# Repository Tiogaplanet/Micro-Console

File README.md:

# Micro-Console
 An Arduboy clone.  I can't think of a witty name.

# Background
This started as a simple project to throw together a PCB with some buttons and an OLED display on which my kids could learn programming and be entertained.  While googling my way to get started I discovered, of course, something like this has already been done and it's called the Arduboy.  It comes with a huge library of games, several community-driven spin-offs, and ports to different MCUs.  There's also the Gamebuino and a bunch of one-off creations enthusiasts have developed but we're going to stick with the Arduboy design here.  Why give up such a huge library of existing software and the community support?

# Design
This project, like the Arduboy, is based on the ATmega32u4.  I'd prefer to use my beloved Wemos D1 mini but I'd rather not use or maintain a ported library, nor do I care to work around the limited IO of the D1 mini.  When the time comes to add Internet access to this device, I will add some form of the ESP8266 with its own library that can co-exist with the Arduboy's library.  This project includes the Winbond W25Q128 SPI flash memory device used in the Arduboy FX.

# Credit
Naturally, credit is owed to Kevin Bates for instigating the whole Arduboy endeavor.

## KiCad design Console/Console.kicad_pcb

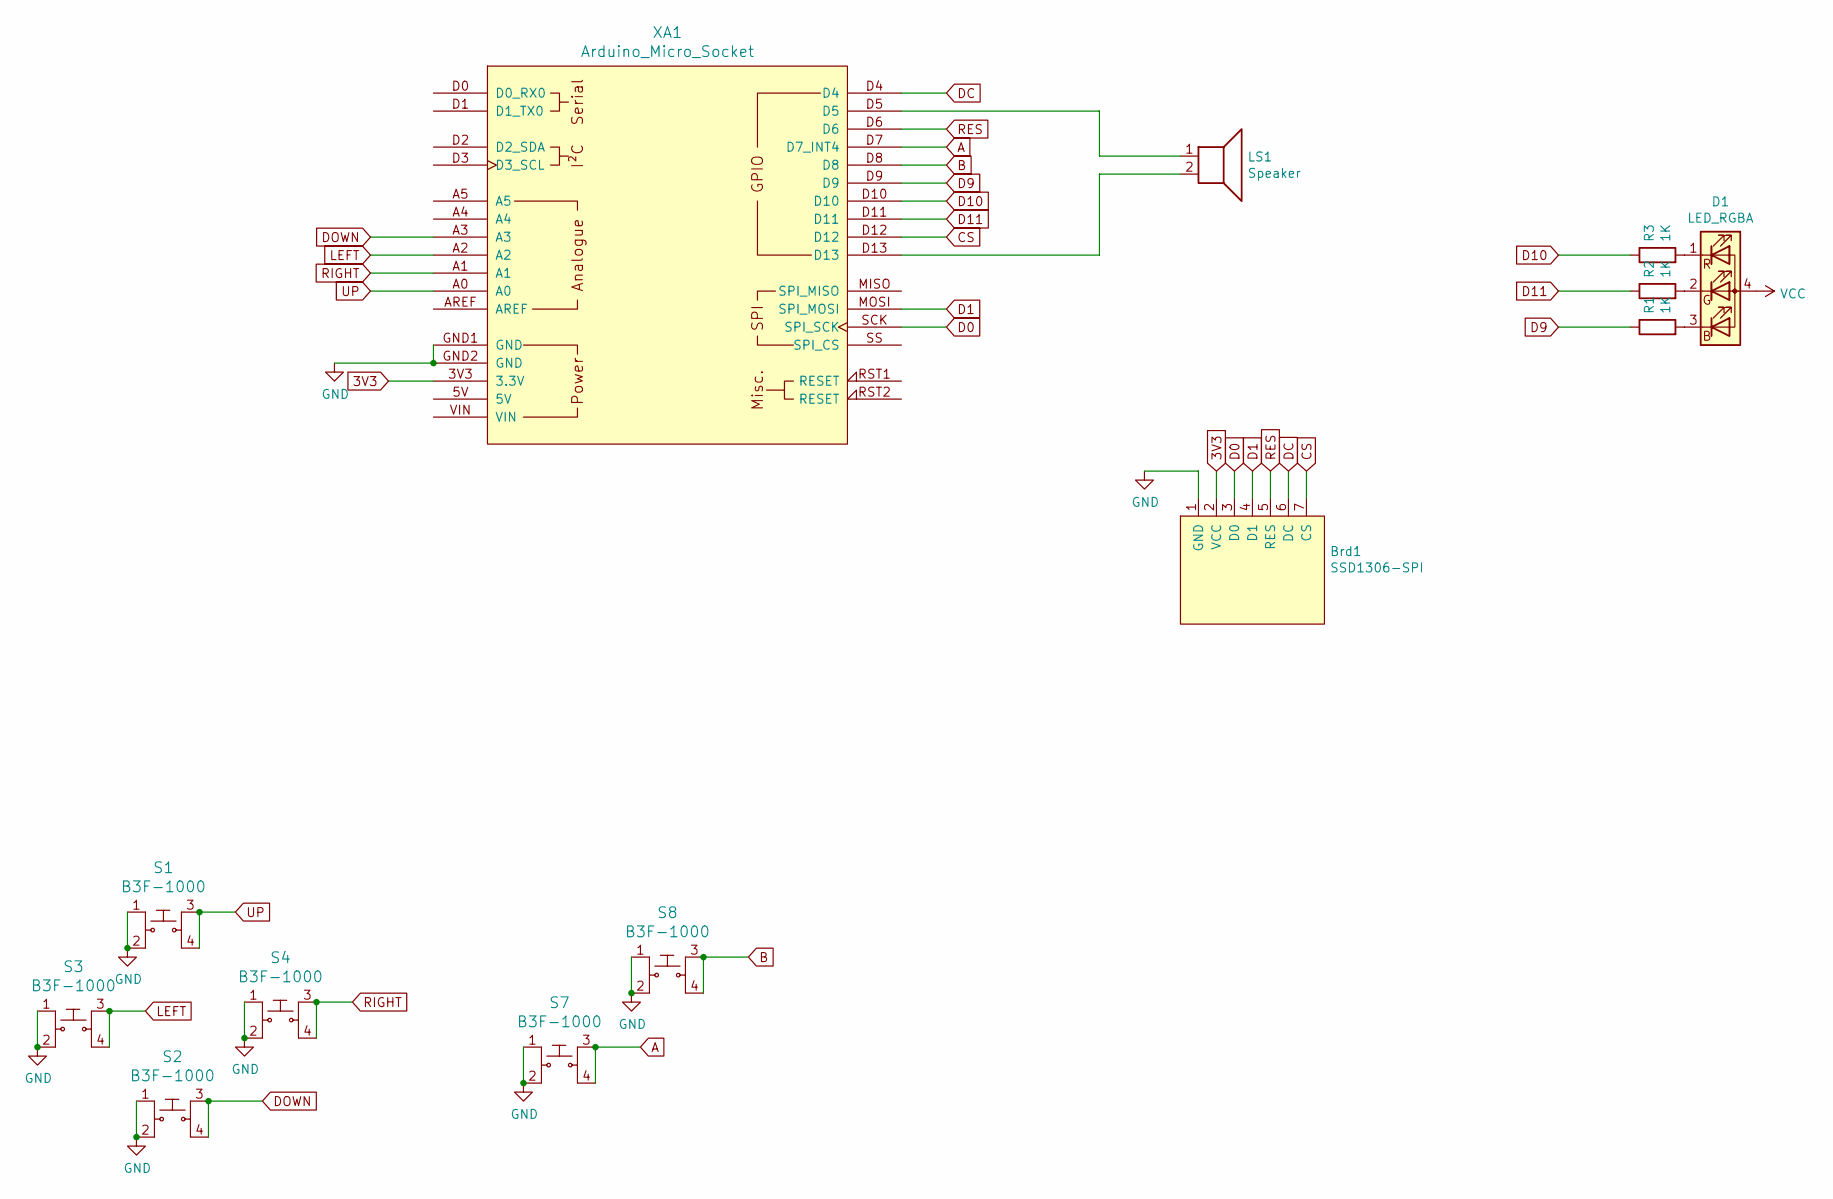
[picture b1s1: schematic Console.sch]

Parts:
Brd1: SSD1306-SPI; 128x64-OLED-SPI
D1: LED_RGBA; LED_BL-FL7680RGB
LS1: Speaker; Buzzer_D14mm_H7mm_P10mm
R1, R2, R3: 1K; R_Axial_DIN0207_L6.3mm_D2.5mm_P7.62mm_Horizontal
S1, S2, S3, S4, S7, S8: B3F-1000; Switch_Tactile_THT_B3F-1xxx; MPN B3F-1000; Digi-Key_PN SW400-ND
XA1: Arduino_Micro_Socket

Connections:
3V3: Brd1.2 (VCC), XA1.3V3 (3.3V)
A: S7.3, S7.4, XA1.D7 (D7_INT4)
B: S8.3, S8.4, XA1.D8
CS: Brd1.7 (CS), XA1.D12
D0: Brd1.3 (D0), XA1.SCK (SPI_SCK)
D1: Brd1.4 (D1), XA1.MOSI (SPI_MOSI)
D9: R1.1, XA1.D9
D10: R3.1, XA1.D10
D11: R2.1, XA1.D11
DC: Brd1.6 (DC), XA1.D4
DOWN: S2.3, S2.4, XA1.A3
GND: Brd1.1 (GND), S1.1, S1.2, S2.1, S2.2, S3.1, S3.2, S4.1, S4.2, S7.1, S7.2, S8.1, S8.2, XA1.GND1 (GND), XA1.GND2 (GND)
LEFT: S3.3, S3.4, XA1.A2
unnamed: D1.1 (RK), R3.2
unnamed: D1.2 (GK), R2.2
unnamed: D1.3 (BK), R1.2
unnamed: LS1.1, XA1.D5
unnamed: LS1.2, XA1.D13
RES: Brd1.5 (RES), XA1.D6
RIGHT: S4.3, S4.4, XA1.A1
UP: S1.3, S1.4, XA1.A0

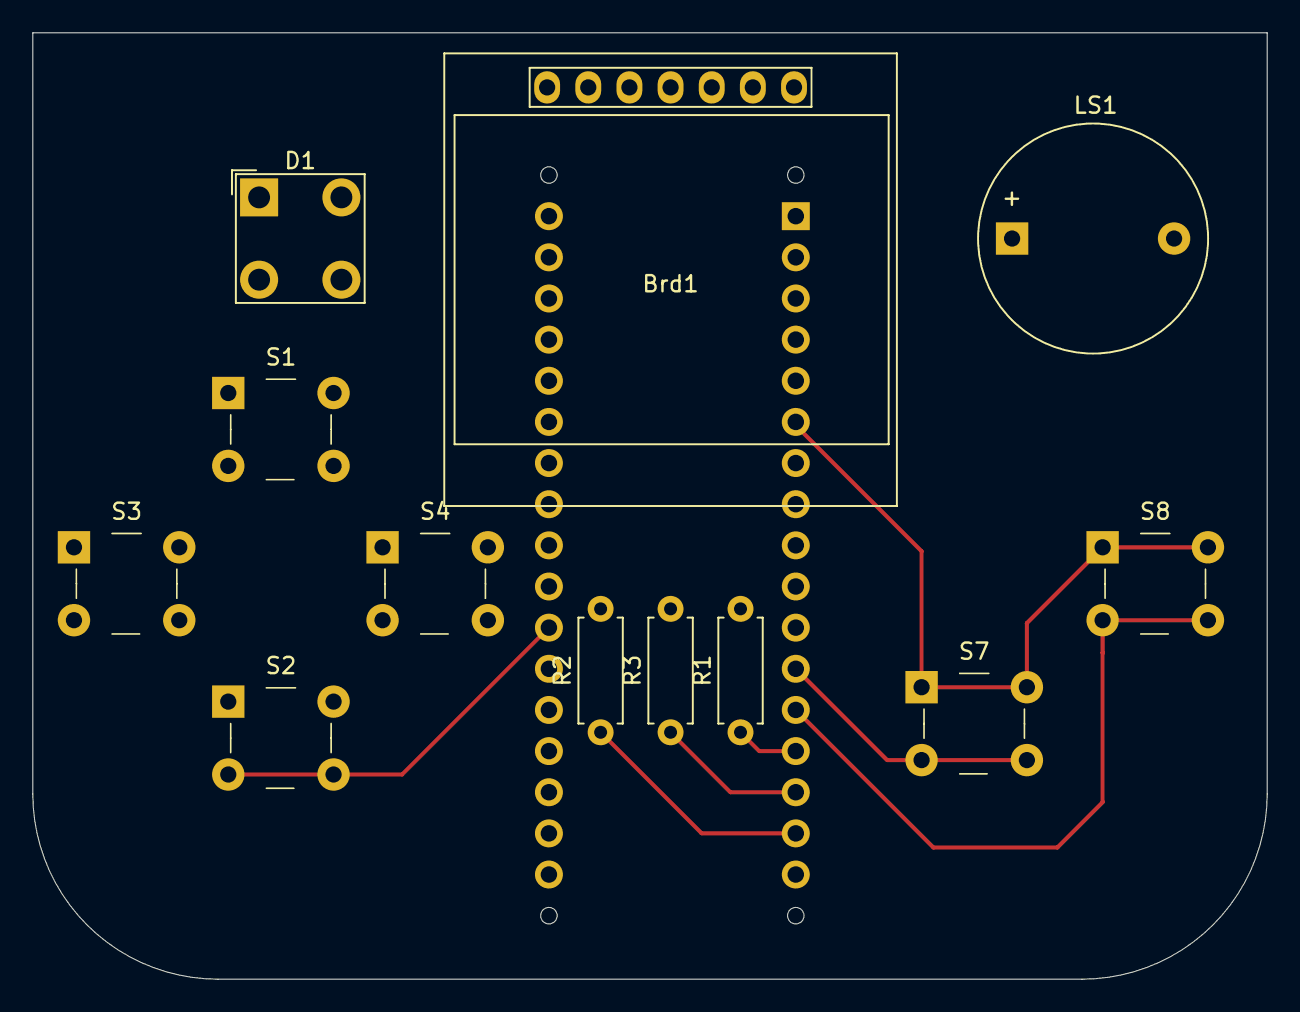
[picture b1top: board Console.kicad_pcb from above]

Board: 2 copper layers, 76.2 x 58.4 mm, 13 parts (1 on the bottom side), 21 nets.

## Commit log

2020-10-28 Initial commit.
    Includes a complete schematic and board layout. Untested.
2020-10-28 Fixing typos and stuff in the readme
